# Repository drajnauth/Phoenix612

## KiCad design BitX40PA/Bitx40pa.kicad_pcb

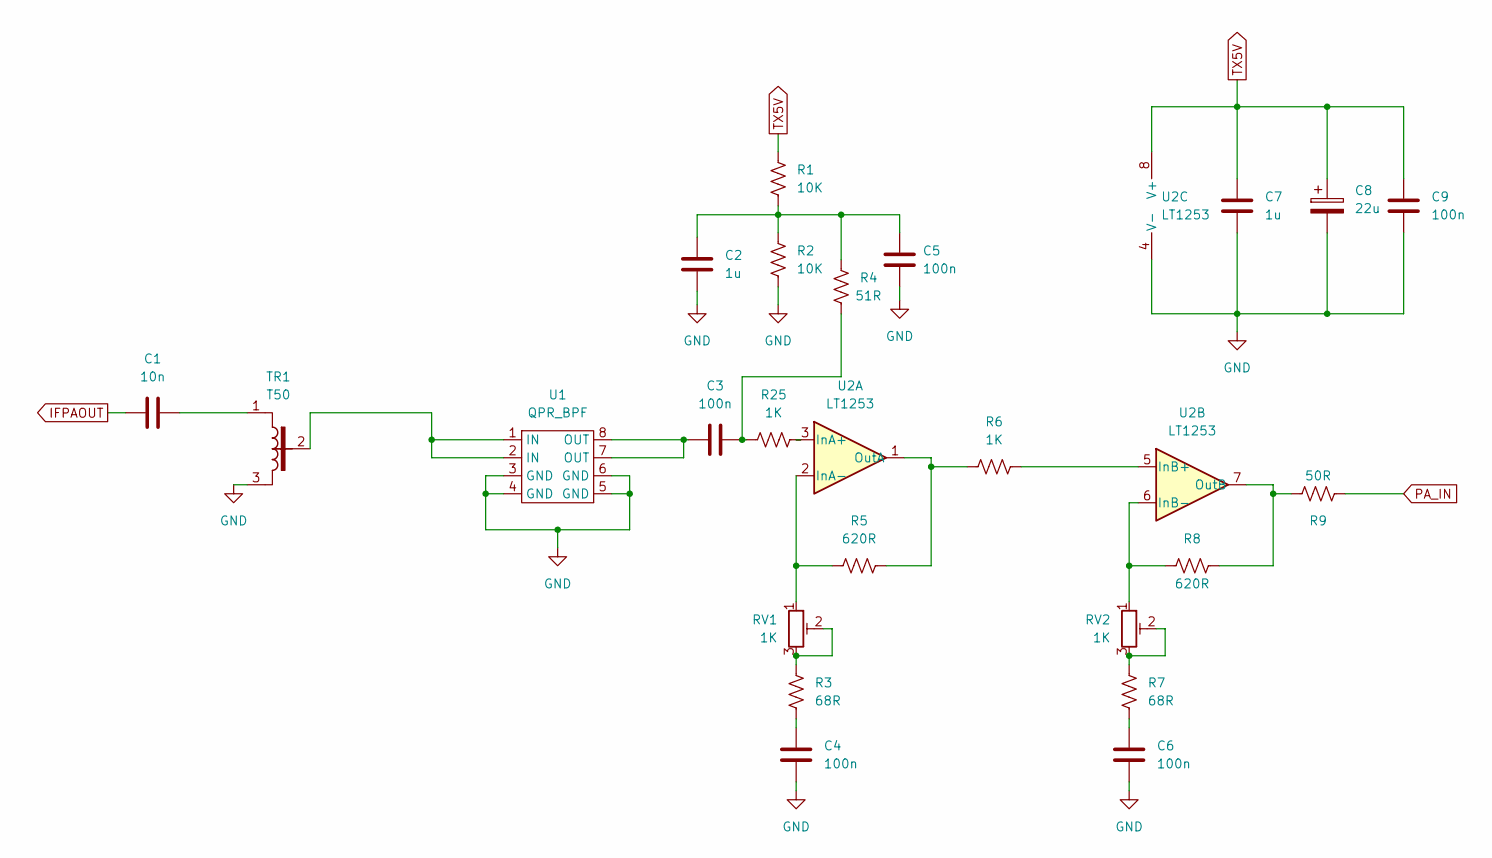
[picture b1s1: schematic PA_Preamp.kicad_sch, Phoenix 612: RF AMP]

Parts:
C1: 10n; C_1206_3216Metric
C2, C7: 1u; C_1206_3216Metric
C3, C4, C5, C6, C9: 100n; C_1206_3216Metric
C8: 22u; CP_Radial_D8.0mm_P2.50mm
R1, R2: 10K; R_1206_3216Metric
R3, R7: 68R; R_1206_3216Metric
R4: 51R; R_1206_3216Metric
R5, R8: 620R; R_1206_3216Metric
R6, R25: 1K; R_1206_3216Metric
R9: 50R; R_1206_3216Metric
RV1, RV2: 1K; Potentiometer_Bourns_3296W_Vertical
TR1: T50; T50-1Tap-Close
U1: QPR_BPF; QRPLabs_Filter_TH
U2: LT1253; DIP-8_W7.62mm

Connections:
GND: C2.2, C4.2, C5.2, C6.2, C7.2, C8.2, C9.2, R2.2, TR1.3, U1.3 (GND), U1.4 (GND), U1.5 (GND), U1.6 (GND), U2.4 (V-); also elsewhere on the board
IFPAOUT: C1.1; also elsewhere on the board
unnamed: C1.2, TR1.1
unnamed: C2.1, C5.1, R1.2, R2.1, R4.2
unnamed: C3.1, U1.7 (OUT), U1.8 (OUT)
unnamed: C3.2, R4.1, R25.1
unnamed: C4.1, R3.2
unnamed: C6.1, R7.2
unnamed: R3.1, RV1.2, RV1.3
unnamed: R5.1, RV1.1, U2.2 (InA-)
unnamed: R5.2, R6.1, U2.1 (OutA)
unnamed: R6.2, U2.5 (InB+)
unnamed: R7.1, RV2.2, RV2.3
unnamed: R8.1, R9.1, U2.7 (OutB)
unnamed: R8.2, RV2.1, U2.6 (InB-)
unnamed: R25.2, U2.3 (InA+)
unnamed: TR1.2, U1.1 (IN), U1.2 (IN)
PA_IN: R9.2; also elsewhere on the board
TX5V: C7.1, C8.1, C9.1, R1.1, U2.8 (V+); also elsewhere on the board

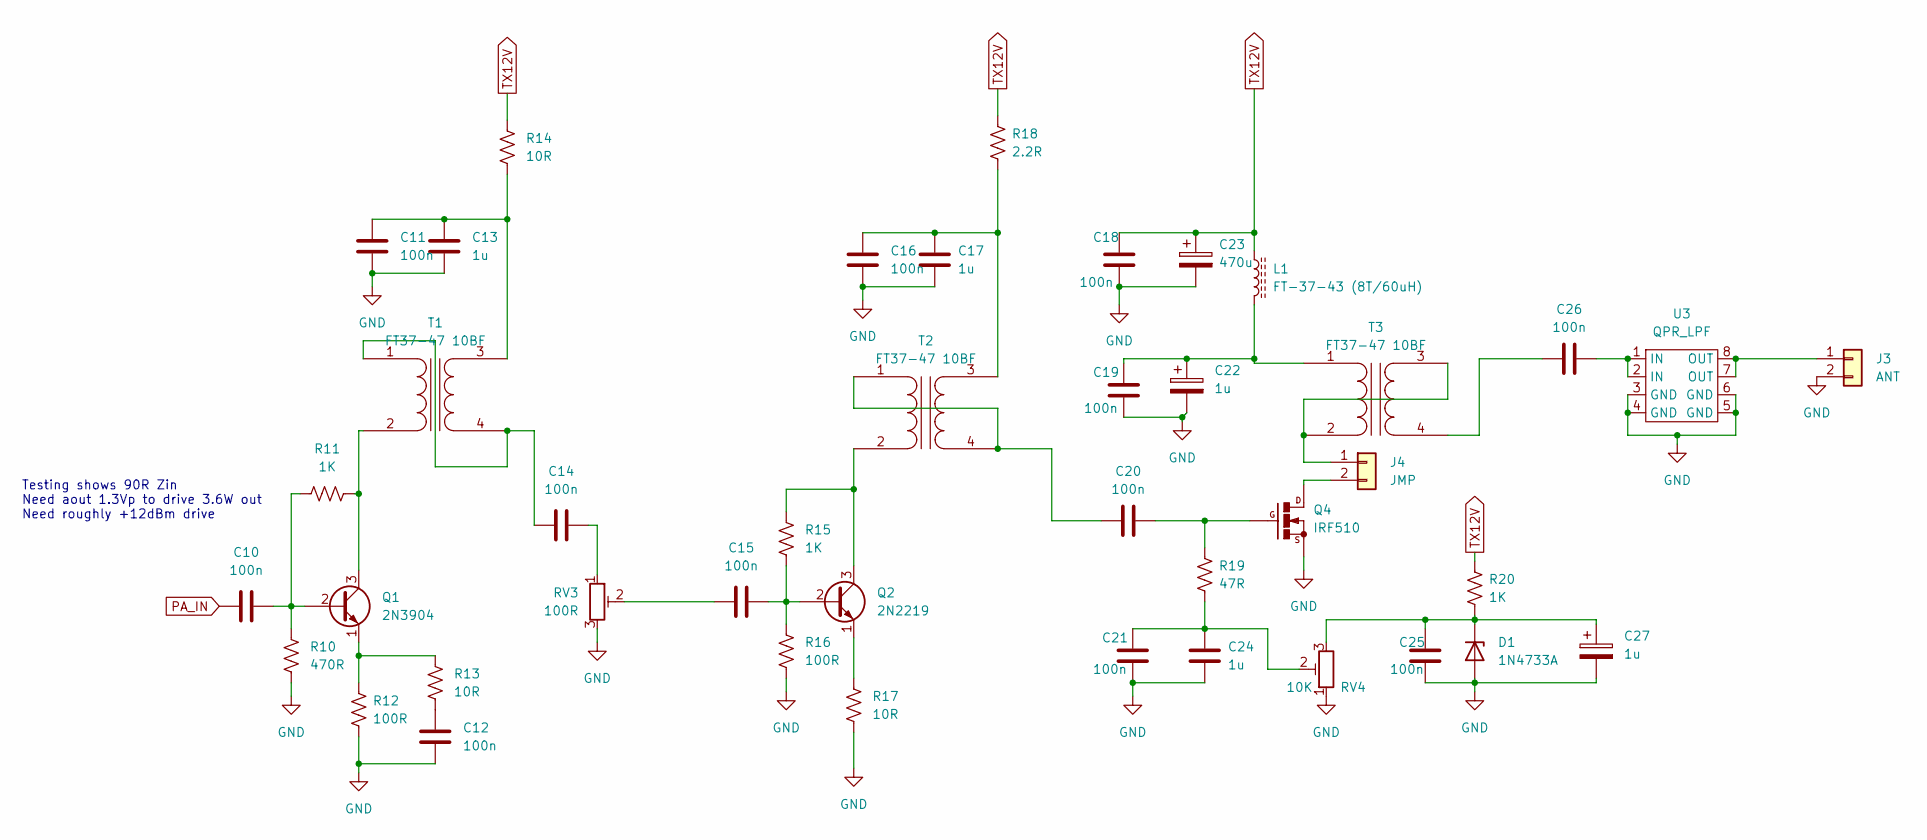
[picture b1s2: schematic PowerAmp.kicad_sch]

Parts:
C10, C11, C12, C14, C15, C16, C18, C19, C20, C21, C25, C26: 100n; C_1206_3216Metric
C13, C17, C24: 1u; C_1206_3216Metric
C22, C27: 1u; CP_Radial_D8.0mm_P2.50mm
C23: 470u; CP_Radial_D8.0mm_P2.50mm
D1: 1N4733A; D_DO-41_SOD81_P10.16mm_Horizontal
J3: ANT; PinHeader_1x02_P2.54mm_Vertical
J4: JMP; PinHeader_1x02_P2.54mm_Vertical
L1: FT-37-43 (8T/60uH); L_Toroid_Horizontal_D9.5mm_P15.00mm_Diameter10-5mm_Amidon-T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
Q1: 2N3904; TO-92_Inline
Q2: 2N2219; TO-39-3
Q4: IRF510; TO-220-3_Vertical
R10: 470R; R_1206_3216Metric
R11, R15, R20: 1K; R_1206_3216Metric
R12, R16: 100R; R_1206_3216Metric
R13, R14, R17: 10R; R_1206_3216Metric
R18: 2.2R; R_1206_3216Metric
R19: 47R; R_1206_3216Metric
RV3: 100R; Potentiometer_Bourns_3296W_Vertical
RV4: 10K; Potentiometer_Bourns_3296W_Vertical
T1, T2, T3: FT37-47 10BF; Transformer_Toroid_Horizontal_D10.5mm_Amidon-T37
U3: QPR_LPF; QRPLabs_Filter_TH

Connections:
GND: C11.2, C12.2, C13.2, C16.2, C17.2, C18.2, C19.2, C21.2, C22.2, C23.2, C24.2, C25.2, C27.2, D1.2 (A), J3.2, Q4.1, R10.1, R12.1, R16.1, R17.1, RV3.3, RV4.1, U3.3 (GND), U3.4 (GND), U3.5 (GND), U3.6 (GND); also elsewhere on the board
unnamed: C10.2, Q1.2 (B), R10.2, R11.1
unnamed: C11.1, C13.1, R14.1, T1.3 (SB)
unnamed: C12.1, R13.1
unnamed: C14.1, T1.1 (AA), T1.4 (SA)
unnamed: C14.2, RV3.1
unnamed: C15.1, RV3.2
unnamed: C15.2, Q2.2 (B), R15.1, R16.2
unnamed: C16.1, C17.1, R18.1, T2.3 (SB)
unnamed: C19.1, C22.1, L1.2, T3.1 (AA)
unnamed: C20.1, T2.1 (AA), T2.4 (SA)
unnamed: C20.2, Q4.3, R19.2
unnamed: C21.1, C24.1, R19.1, RV4.2
unnamed: C25.1, C27.1, D1.1 (K), R20.2, RV4.3
unnamed: C26.1, T3.4 (SA)
unnamed: C26.2, U3.1 (IN), U3.2 (IN)
unnamed: J3.1, U3.7 (OUT), U3.8 (OUT)
unnamed: Q1.1 (E), R12.2, R13.2
unnamed: Q1.3 (C), R11.2, T1.2 (AB)
unnamed: Q2.1 (E), R17.2
unnamed: Q2.3 (C), R15.2, T2.2 (AB)
unnamed: J4.2, Q4.2
unnamed: J4.1, T3.2 (AB), T3.3 (SB)
PA_IN: C10.1; also elsewhere on the board
TX12V: C18.1, C23.1, L1.1, R14.2, R18.2, R20.1; also elsewhere on the board

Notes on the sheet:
Testing shows 90R Zin Need aout 1.3Vp to drive 3.6W out Need roughly +12dBm drive

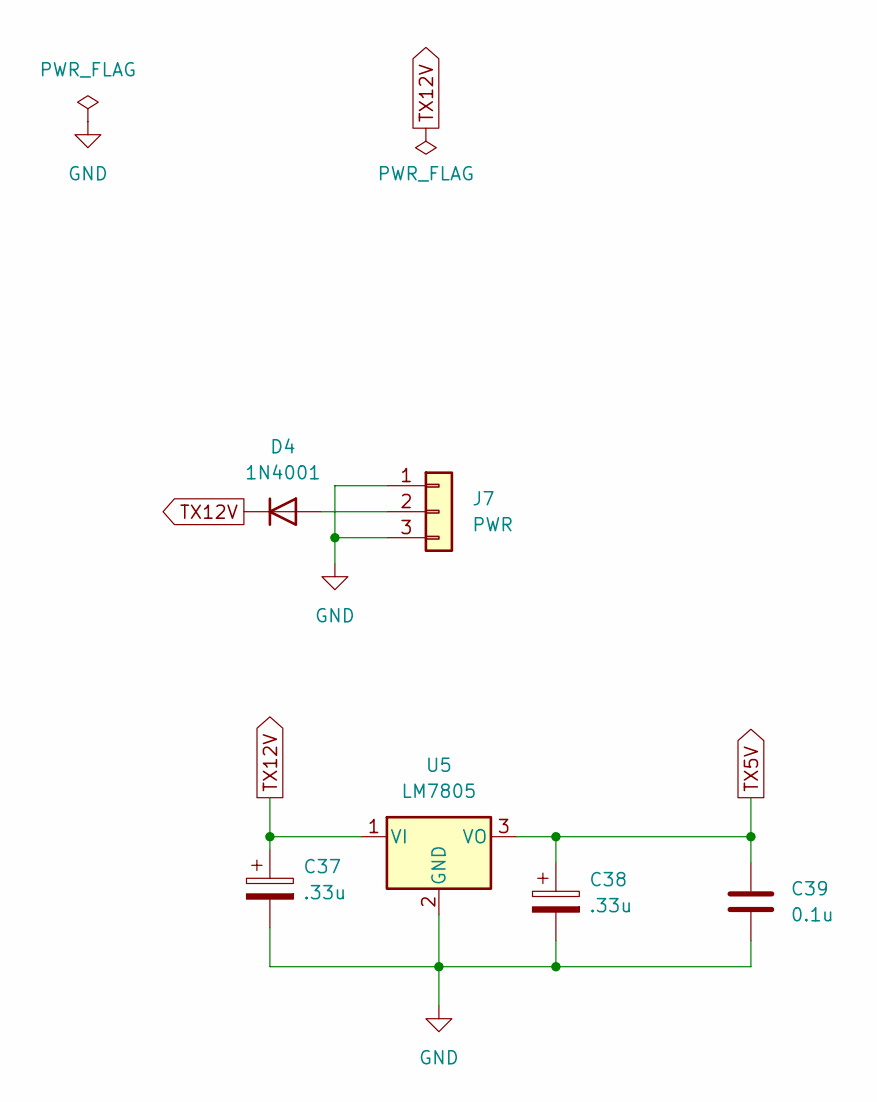
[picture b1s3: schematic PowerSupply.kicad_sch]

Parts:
C37, C38: .33u; CP_Radial_D8.0mm_P2.50mm
C39: 0.1u; C_1206_3216Metric
D4: 1N4001; D_DO-41_SOD81_P10.16mm_Horizontal
J7: PWR; PinHeader_1x03_P2.54mm_Vertical
U5: LM7805; TO-220-3_Vertical

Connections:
GND: C37.2, C38.2, C39.2, J7.1, J7.3, U5.2 (GND); also elsewhere on the board
unnamed: D4.2 (A), J7.2
TX5V: C38.1, C39.1, U5.3 (VO); also elsewhere on the board
TX12V: C37.1, D4.1 (K), U5.1 (VI); also elsewhere on the board

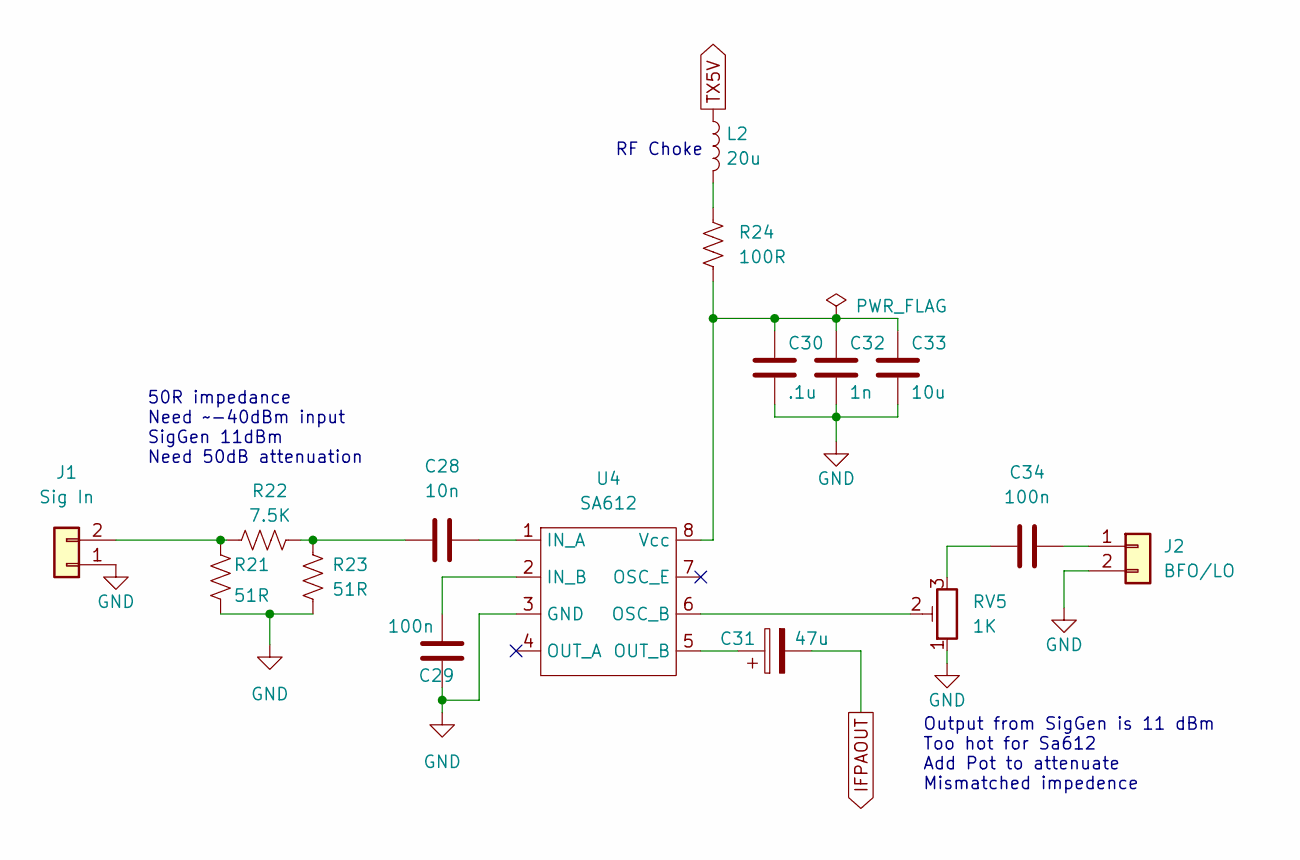
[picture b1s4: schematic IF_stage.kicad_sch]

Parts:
C28: 10n; C_1206_3216Metric
C29, C34: 100n; C_1206_3216Metric
C30: .1u; C_1206_3216Metric
C31: 47u; CP_Radial_D8.0mm_P2.50mm
C32: 1n; C_1206_3216Metric
C33: 10u; C_1206_3216Metric
J1: Sig In; PinHeader_1x02_P2.54mm_Vertical
J2: BFO/LO; PinHeader_1x02_P2.54mm_Vertical
L2: 20u; L_1206_3216Metric
R21, R23: 51R; R_1206_3216Metric
R22: 7.5K; R_1206_3216Metric
R24: 100R; R_1206_3216Metric
RV5: 1K; Potentiometer_Bourns_3296W_Vertical
U4: SA612; DIP-8_W7.62mm_Socket

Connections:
GND: C29.2, C30.2, C32.2, C33.2, J1.1, J2.2, R21.2, R23.2, RV5.1, U4.3 (GND); also elsewhere on the board
IFPAOUT: C31.2; also elsewhere on the board
unnamed: C28.1, R22.2, R23.1
unnamed: C28.2, U4.1 (IN_A)
unnamed: C29.1, U4.2 (IN_B)
unnamed: C30.1, C32.1, C33.1, R24.2, U4.8 (Vcc)
unnamed: C31.1, U4.5 (OUT_B)
unnamed: C34.1, J2.1
unnamed: C34.2, RV5.3
unnamed: J1.2, R21.1, R22.1
unnamed: L2.2, R24.1
unnamed: RV5.2, U4.6 (OSC_B)
TX5V: L2.1; also elsewhere on the board

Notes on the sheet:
Output from SigGen is 11 dBm Too hot for Sa612 Add Pot to attenuate Mismatched impedence
RF Choke
50R impedance Need ~-40dBm input SigGen 11dBm Need 50dB attenuation

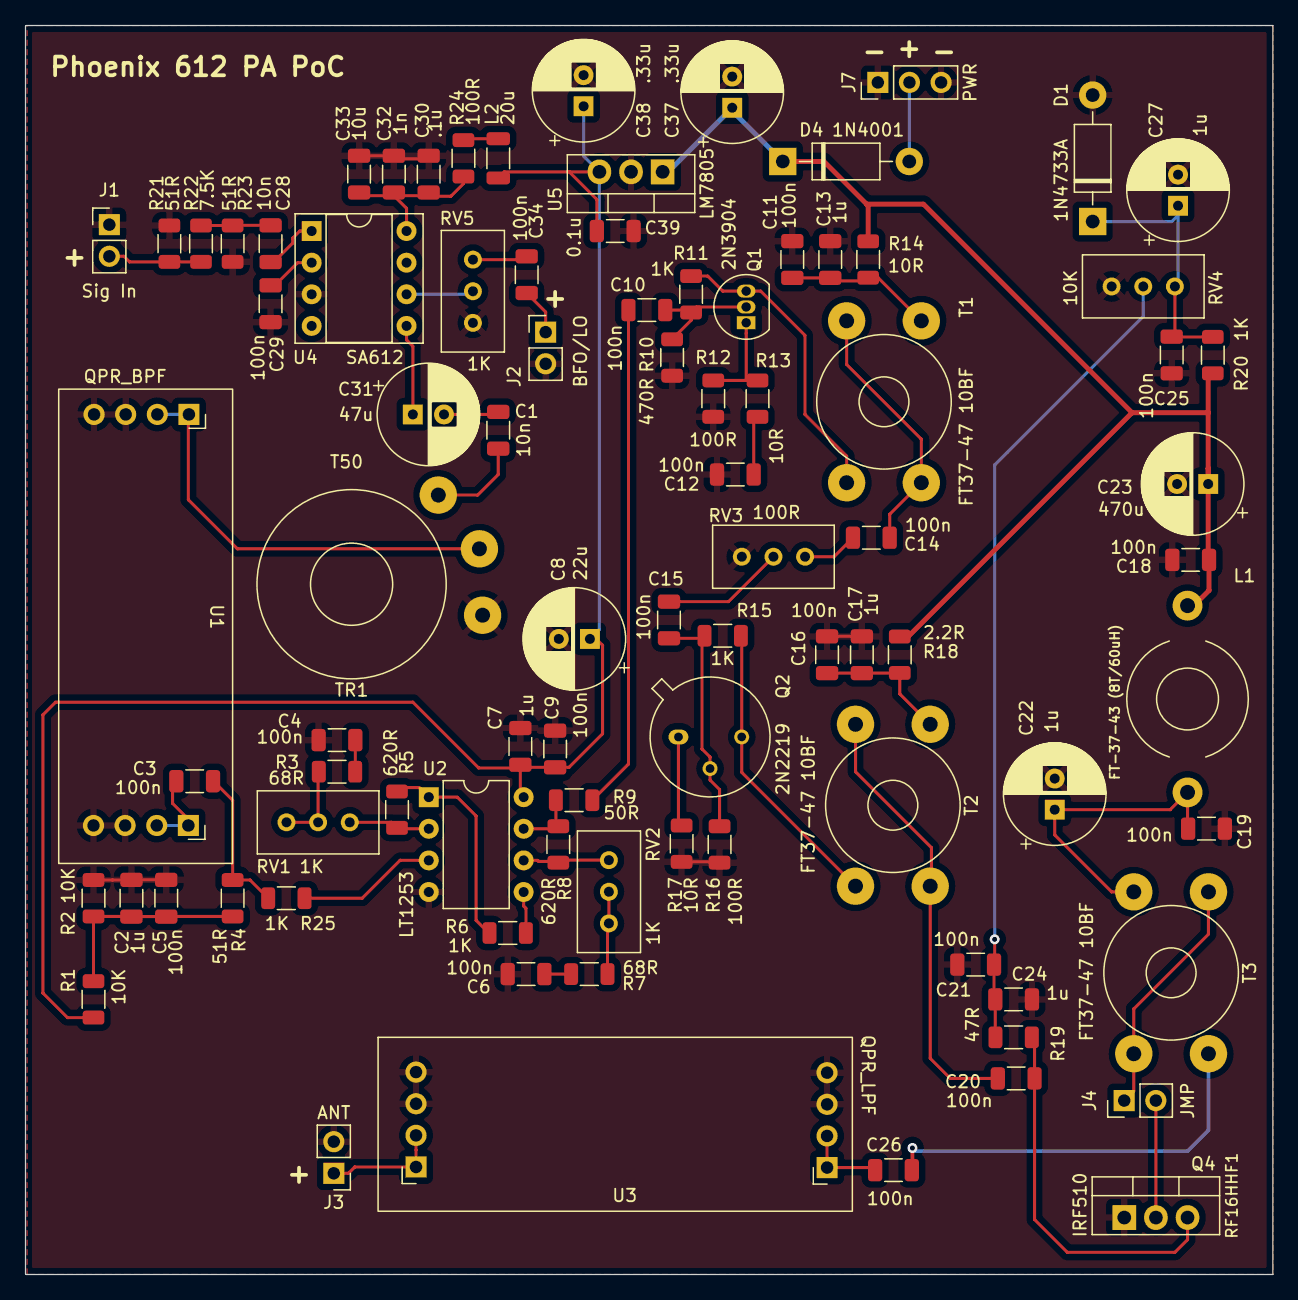
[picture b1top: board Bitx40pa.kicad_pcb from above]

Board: 2 copper layers, 100.2 x 100.3 mm, 88 parts (0 on the bottom side), 53 nets.

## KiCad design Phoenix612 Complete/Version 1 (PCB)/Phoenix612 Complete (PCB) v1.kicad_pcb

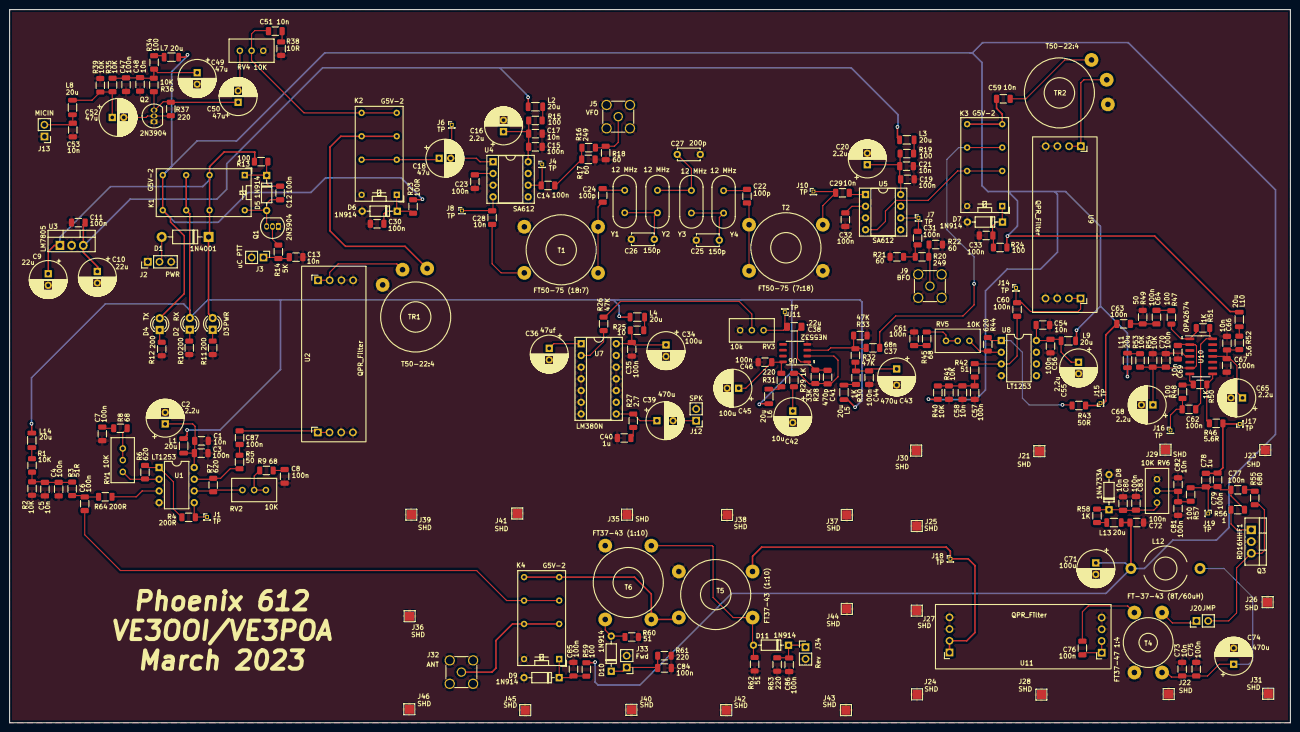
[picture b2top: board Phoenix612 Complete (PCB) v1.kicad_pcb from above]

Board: 2 copper layers, 277.9 x 154.7 mm, 257 parts (0 on the bottom side), 130 nets.

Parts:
C1, C5, C13, C17, C21, C28, C29, C48, C51, C53, C54, C58, C59, C66, C69, C73, C80, C82: 10n; C_1206_3216Metric
C2, C16, C20, C55, C65, C68: 2.2u; CP_Radial_D8.0mm_P2.50mm
C3, C4, C6, C7, C8, C11, C12, C14, C15, C19, C23, C30, C31, C32, C33, C35, C44, C46, C47, C56, C57, C60, C61, C62, C63, C64, C67, C70, C72, C75, C76, C77, C79, C81, C83, C84, C85, C86, C87: 100n; C_1206_3216Metric
C9, C10: 22u; CP_Radial_D8.0mm_P2.50mm
C18, C49, C50, C52: 47u; CP_Radial_D8.0mm_P2.50mm
C22, C24: 100p; C_1206_3216Metric
C25, C26: 150p; C_Disc_D4.7mm_W2.5mm_P5.00mm
C27: 200p; C_Disc_D4.7mm_W2.5mm_P5.00mm
C34, C45, C71: 100u; CP_Radial_D8.0mm_P2.50mm
C36: 47uf; CP_Radial_D8.0mm_P2.50mm
C37: 68n; C_1206_3216Metric
C38: .22u; C_1206_3216Metric_Pad1.33x1.80mm_HandSolder
C39, C43, C74: 470u; CP_Radial_D8.0mm_P3.50mm
C40, C78: 1u; C_1206_3216Metric
C41: 470p; C_1206_3216Metric
C42: 10u; CP_Radial_D8.0mm_P2.50mm
D1: 1N4001; D_DO-41_SOD81_P10.16mm_Horizontal
D2: RX; LED_D3.0mm
D3: PWR; LED_D3.0mm
D4: TX; LED_D3.0mm
D5, D6, D7, D9, D10, D11: 1N914; D_DO-35_SOD27_P7.62mm_Horizontal
D8: 1N4733A; D_DO-35_SOD27_P7.62mm_Horizontal
J1, J4, J6, J7, J8, J10, J11, J14, J15, J16, J17, J18, J19: TP; PinHeader_1x01_P1.00mm_Vertical
J2: PWR; PinHeader_1x03_P2.54mm_Vertical
J3: uC PTT; PinHeader_1x02_P2.54mm_Vertical
J5: VFO; SMA_Amphenol_901-144_Vertical
J9: BFO; SMA_Amphenol_901-144_Vertical
J12: SPK; PinHeader_1x02_P2.54mm_Vertical
J13: MICIN; PinHeader_1x02_P2.54mm_Vertical
J20: JMP; PinHeader_1x02_P2.54mm_Vertical
J21, J22, J23, J24, J25, J26, J27, J28, J29, J30, J31, J35, J36, J37, J38, J39, J40, J41, J42, J43, J44, J45, J46: SHD; TestPoint_Pad_2.0x2.0mm
J32: ANT; SMA_Amphenol_901-144_Vertical
J33: Fwd; PinHeader_1x02_P2.54mm_Vertical
J34: Rev; PinHeader_1x02_P2.54mm_Vertical
K1, K2, K3, K4: G5V-2; Relay_DPDT_Omron_G5V-2
L1, L2, L3, L4, L5, L6, L7, L8, L9, L10, L11, L13, L14: 20u; L_1206_3216Metric
L12: FT-37-43 (8T/60uH); L_Toroid_Horizontal_D9.5mm_P15.00mm_Diameter10-5mm_Amidon-T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
Q1, Q2: 2N3904; TO-92_Inline
Q3: RD16HHF1; TO-220-3
R1, R2, R35, R36, R39, R40, R41, R53, R54: 10K; R_1206_3216Metric
R3: 51R; R_1206_3216Metric
R4, R64: 200R; R_1206_3216Metric
R5, R49: 50; R_1206_3216Metric
R6, R7, R44: 620; R_1206_3216Metric
R8, R9, R45: 68; R_1206_3216Metric
R10, R11, R12: 200; R_1206_3216Metric
R13, R15, R19, R24, R34, R47, R48, R57, R59: 100; R_1206_3216Metric
R14: 5K; R_1206_3216Metric
R16, R20: 249; R_1206_3216Metric
R17, R18, R21, R22: 60; R_1206_3216Metric
R23: 100R; R_1206_3216Metric
R25: 10; R_1206_3216Metric
R26, R32, R33: 47K; R_1206_3216Metric
R27: 2.7; R_1206_3216Metric
R28: 33K; R_1206_3216Metric
R29, R30, R50, R51, R58: 1K; R_1206_3216Metric
R31, R37, R61, R63: 220; R_1206_3216Metric
R38: 10R; R_1206_3216Metric
R42, R60, R62: 51; R_1206_3216Metric
R43: 50R; R_1206_3216Metric
R46: 5.6R; R_1206_3216Metric
R52: 5.6; R_1206_3216Metric
R55: 680; R_1206_3216Metric
R56: 1; R_1206_3216Metric
RV1, RV2, RV4, RV5, RV6: 10K; Potentiometer_Bourns_3296W_Vertical
RV3: 10k; Potentiometer_Bourns_3296W_Vertical
T1: FT50-75 (18:7); Transformer_Toroid_Horizontal_D14.0mm_Amidon-T50
T2: FT50-75 (7:18); Transformer_Toroid_Horizontal_D14.0mm_Amidon-T50
T4: FT37-47 1:4; Transformer_Toroid_Horizontal_D10.5mm_Amidon-T37
T5, T6: FT37-43 (1:10); Transformer_Toroid_Horizontal_D14.0mm_Amidon-T50
TR1, TR2: T50-22:4; T50-1Tap-Close
U1, U8: LT1253; DIP-8_W7.62mm
U2, U9, U11: QPR_Filter; QRPLabs_Filter_TH
U3: LM7805; TO-220-3_Vertical
U4, U5: SA612; DIP-8_W7.62mm_Socket
U6: NE5532; SOP-8_3.9x4.9mm_P1.27mm
U7: LM380N; DIP-14_W7.62mm_Socket
U10: OPA2674; SOIC-14_3.9x8.7mm_P1.27mm
Y1, Y2, Y3, Y4: 12 MHz; Crystal_HC49-4H_Vertical

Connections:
5V: C10.1, C11.1, L2.1, L3.1, U3.3 (VO)
12V: C9.1, D1.1 (K), D3.2 (A), K1.4, K1.13, R13.2, U3.1 (VI)
AF_12V: C45.1, C46.1, R31.2, U6.8 (V+)
AF_BIAS: C37.2, R32.1, R33.1, U6.3 (+)
ANT: J32.1 (In), K4.4, K4.13
ANT_IN: C6.1, K4.6, K4.11
ANT_OUT: K4.8, K4.9, T5.4 (SB), T6.1 (AA)
GND: C1.2, C2.2, C3.2, C4.2, C5.2, C7.2, C8.2, C9.2, C10.2, C11.2, C13.1, C15.2, C16.2, C17.2, C19.2, C20.2, C21.2, C23.2, C25.2, C26.2, C27.2, C30.2, C32.2, C33.2, C34.2, C35.2, C36.2, C40.2, C42.2, C43.2, C44.2, C45.2, C46.2, C47.2, C48.2, C49.2, C53.2, C54.2, C55.2, C56.2, C57.2, C58.2, C61.2, C65.2, C66.2, C67.2, C68.2, C69.2, C70.2, C71.2, C72.2, C73.2, C74.2, C75.2, C80.2, C81.2, C82.2, C83.2, C84.2, C85.2, C86.2, D6.2 (A), D7.2 (A), D8.2 (A), D9.2 (A), J2.1, J2.3, J3.2, J5.2 (Ext), J9.2 (Ext), J12.2, J13.1, J21.1, J22.1, J23.1, J24.1, J25.1, J26.1, J27.1, J28.1, J29.1, J30.1, J31.1, J32.2 (Ext), J33.2, J34.2, J35.1, J36.1, J37.1, J38.1, J39.1, J40.1, J41.1, J42.1, J43.1, J44.1, J45.1, J46.1, K2.16, K3.16, K4.16, Q1.1 (E), Q2.1 (E), Q3.2, R2.2, R10.2, R11.2, R12.2, R17.2, R18.2, R21.2, R22.2, R33.2, R38.1, R39.2, R41.2, R49.1, R54.2, R60.1, R61.1, R62.1, R63.1, RV3.3, RV4.3, RV6.1, T1.3 (SA), T2.2 (AB), T4.3 (SB), T5.2 (AB), T6.4 (SB), TR1.1, TR2.3, U1.4 (V-), U2.3 (GND), U2.4 (GND), U2.5 (GND), U2.6 (GND), U3.2 (GND), U4.3 (GND), U5.3 (GND), U6.4 (V-), U7.3 (GND), U7.4 (GND), U7.5 (GND), U7.6 (-), U7.7 (GND), U7.10 (GND), U7.11 (GND), U7.12 (GND), U8.4 (V-), U9.3 (GND), U9.4 (GND), U9.5 (GND), U9.6 (GND), U10.4 (V-), U11.3 (GND), U11.4 (GND), U11.5 (GND), U11.6 (GND)
IFAFOUT: C37.1, K3.6, K3.11
IFMICIN: C51.1, K2.8, K2.9, RV4.2
IFPAOUT: C59.1, K3.8, K3.9
IFRFIN: K2.6, K2.11, TR1.3
M2_12V: C73.1, C74.1, C75.1, L12.2, T4.1 (AA)
unnamed: C1.1, C2.1, C3.1, L1.2, U1.8 (V+)
unnamed: C4.1, C5.1, R1.2, R2.1, R3.2
unnamed: C6.2, R3.1, R64.1
unnamed: C7.1, R8.2
unnamed: C8.1, R9.2
unnamed: C12.1, D5.1 (K), K1.1, R13.1
unnamed: C12.2, D5.2 (A), K1.16, Q1.3 (C)
unnamed: C13.2, J3.1, R14.2
unnamed: C14.1, R16.1, R17.1
unnamed: C14.2, J4.1, U4.6 (OSC_B)
unnamed: C15.1, C16.1, C17.1, R15.2, U4.8 (Vcc)
unnamed: C18.1, K2.4, K2.13
unnamed: C18.2, J6.1, U4.1 (IN_A)
unnamed: C19.1, C20.1, C21.1, R19.2, U5.8 (Vcc)
unnamed: C22.1, Y4.2
unnamed: C22.2, T2.1 (AA), T2.3 (SA)
unnamed: C23.1, U4.2 (IN_B)
unnamed: C24.1, T1.2 (AB), T1.4 (SB)
unnamed: C24.2, Y1.1
unnamed: C25.1, Y3.2, Y4.1
unnamed: C26.1, Y1.2, Y2.1
unnamed: C27.1, Y2.2, Y3.1
unnamed: C28.1, J8.1, U4.4 (OUT_A)
unnamed: C28.2, T1.1 (AA)
unnamed: C29.1, J10.1, T2.4 (SB)
unnamed: C29.2, U5.1 (IN_A)
unnamed: C30.1, D6.1 (K), K2.1, R23.1
unnamed: C31.1, R20.1, R21.1
unnamed: C31.2, J7.1, U5.6 (OSC_B)
unnamed: C32.1, U5.2 (IN_B)
unnamed: C33.1, D7.1 (K), K3.1, R24.1
unnamed: C34.1, C35.1, R25.2, U7.14 (VS)
unnamed: C36.1, U7.1 (BYPASS)
unnamed: C38.1, C41.2, R28.2, U6.1
unnamed: C38.2, J11.1, RV3.1
unnamed: C39.1, R27.1, U7.8
unnamed: C39.2, J12.1
unnamed: C40.1, R27.2
unnamed: C41.1, R28.1, R29.1, U6.2 (-)
unnamed: C42.1, R29.2
unnamed: C43.1, C44.1, R30.2, R32.2
unnamed: C47.1, C48.1, C49.1, R34.2, R35.1, R36.1
unnamed: C50.1, Q2.3 (C), R36.2, R37.2
unnamed: C50.2, RV4.1
unnamed: C51.2, R38.2
unnamed: C52.1, L8.2, R35.2, R39.1
unnamed: C52.2, Q2.2 (B), R37.1
unnamed: C53.1, J13.2, L8.1
unnamed: C54.1, C55.1, C56.1, L9.2, U8.8 (V+)
unnamed: C57.1, C58.1, R40.2, R41.1, R42.2
unnamed: C59.2, TR2.1
unnamed: C60.1, J14.1, U9.7 (OUT), U9.8 (OUT)
unnamed: C60.2, R42.1, U8.3 (InA+)
unnamed: C61.1, R45.2
unnamed: C62.1, R51.2, U10.14
unnamed: C62.2, J16.1, R48.1
unnamed: C63.2, C64.1, R49.2
unnamed: C64.2, R47.1
unnamed: C76.1, T4.4 (SA)
unnamed: C76.2, U11.1 (IN), U11.2 (IN)
unnamed: C77.1, R55.2
unnamed: C77.2, C78.1, C79.1, J19.1, R56.2, R57.2
unnamed: C80.1, C83.1, D8.1 (K), R58.2, RV6.3
unnamed: C81.1, C82.1, R57.1, RV6.2
unnamed: C84.1, D10.1 (K), J33.1, R61.2
unnamed: C85.1, D9.1 (K), K4.1, R59.1
unnamed: C86.1, D11.1 (K), J34.1, R63.2
unnamed: D1.2 (A), J2.2
unnamed: D2.1 (K), R10.1
unnamed: D3.1 (K), R11.1
unnamed: D4.1 (K), R12.1
unnamed: D10.2 (A), R60.2, T6.3 (SA)
unnamed: D11.2 (A), R62.2, T5.3 (SA), T6.2 (AB)
unnamed: J1.1, R4.2, U1.5 (InB+)
unnamed: J5.1 (In), R16.2, R18.1
unnamed: J9.1 (In), R20.2, R22.1
unnamed: J20.1, T4.2 (AB)
unnamed: J20.2, Q3.3, R55.1
unnamed: K3.4, K3.13, U5.4 (OUT_A)
unnamed: L2.2, R15.1
unnamed: L3.2, R19.1
unnamed: L4.2, R25.1
unnamed: L5.2, R30.1
unnamed: L6.2, R31.1
unnamed: L7.2, R34.1
unnamed: L10.1, R52.1
unnamed: L11.1, R53.1
unnamed: L13.1, R58.1
unnamed: Q1.2 (B), R14.1
unnamed: Q3.1, R56.1
unnamed: L14.2, R1.1
unnamed: R4.1, R6.2, U1.1 (OutA)
unnamed: R5.1, R7.1, U1.7 (OutB)
unnamed: C87.1, R5.2
unnamed: R6.1, RV1.1, U1.2 (InA-)
unnamed: R7.2, RV2.1, U1.6 (InB-)
unnamed: R8.1, RV1.2, RV1.3
unnamed: R9.1, RV2.2, RV2.3
unnamed: R26.1, RV3.2
unnamed: R26.2, U7.2 (+)
unnamed: R43.1, R44.2, U8.1 (OutA)
unnamed: R44.1, RV5.1, U8.2 (InA-)
unnamed: R45.1, RV5.2, RV5.3
unnamed: R46.1, R50.2, U10.8
unnamed: R47.2, R51.1, U10.1 (-)
unnamed: R48.2, R50.1, U10.7 (-)
unnamed: R64.2, U1.3 (InA+)
unnamed: C87.2, U2.1 (IN), U2.2 (IN)
unnamed: TR1.2, U2.7 (OUT), U2.8 (OUT)
unnamed: TR2.2, U9.1 (IN), U9.2 (IN)
PA_DRIVER_IN: C63.1, J15.1, R43.2
PA_IN: C78.2, C79.2, J17.1, R46.2
PA_OUT: J18.1, T5.1 (AA), U11.7 (OUT), U11.8 (OUT)
RX12V: D2.2 (A), K1.6, K1.11, L1.1, L4.1, L5.1, L6.1, L14.1
TX12V: C71.1, C72.1, D4.2 (A), K1.8, K1.9, L7.1, L9.1, L10.2, L11.2, L12.1, L13.2, R23.2, R24.2, R40.1, R59.2
U1_6V: C68.1, C69.1, C70.1, R53.2, R54.1, U10.2 (+), U10.6 (+)
U1_12V: C65.1, C66.1, C67.1, R52.2, U10.11 (V+)

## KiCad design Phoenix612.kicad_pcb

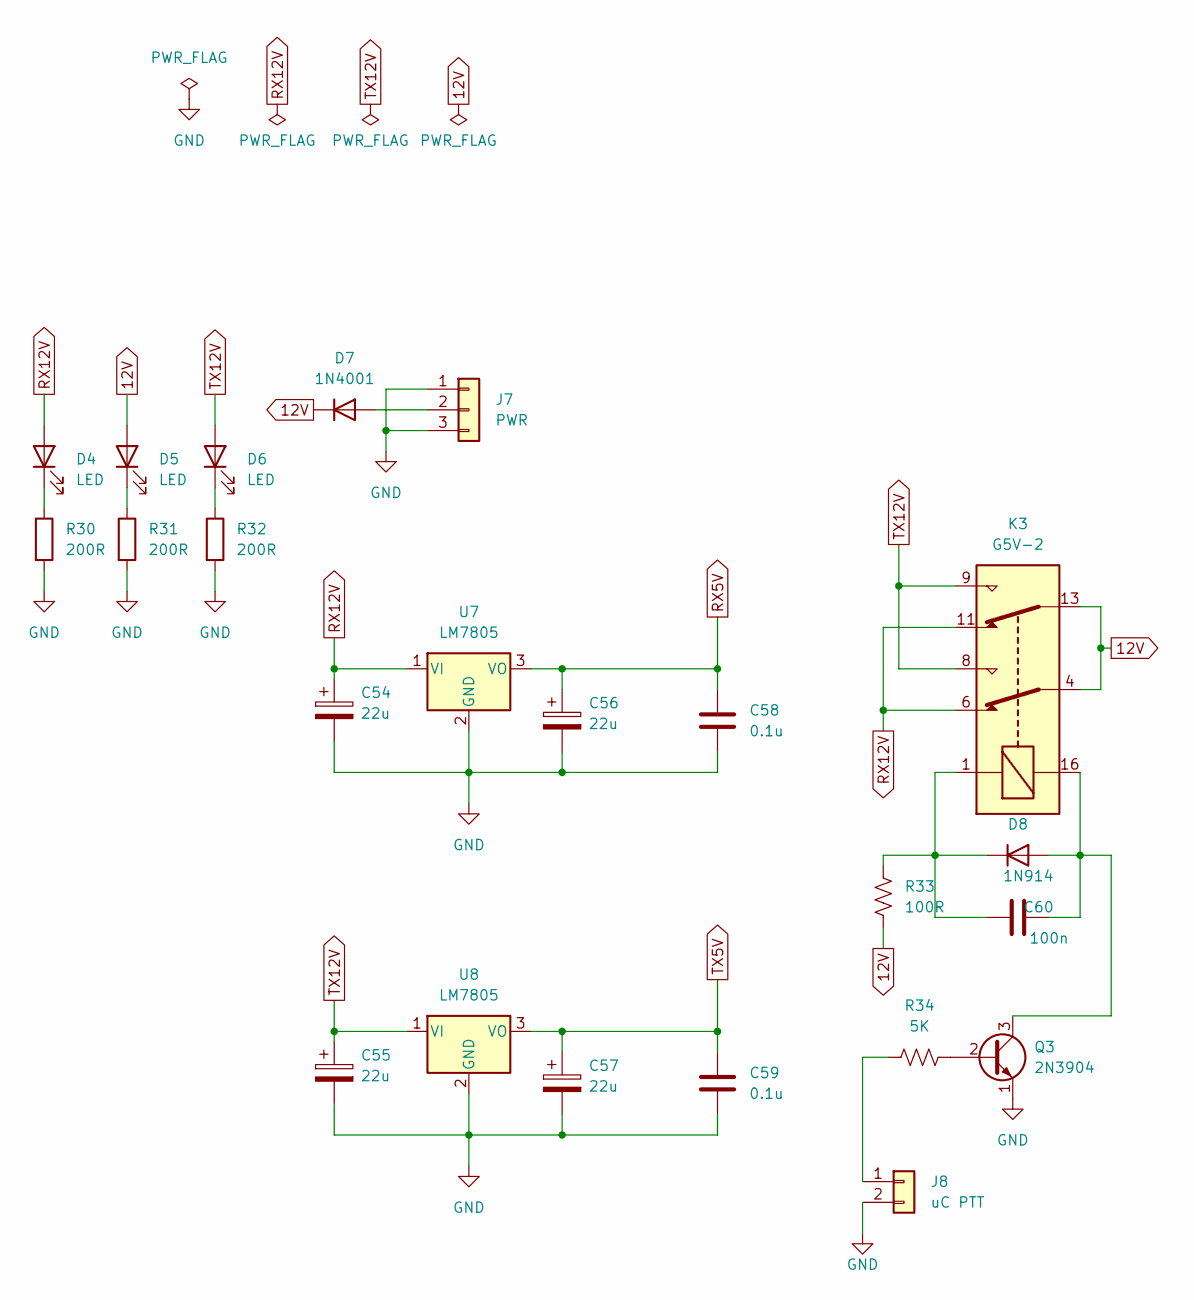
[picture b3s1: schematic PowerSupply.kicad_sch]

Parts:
C54, C55, C56, C57: 22u; CP_Radial_D8.0mm_P2.50mm
C58, C59: 0.1u; C_Disc_D3.0mm_W1.6mm_P2.50mm
C60: 100n; C_Disc_D3.4mm_W2.1mm_P2.50mm
D4, D5, D6: LED; LED_D3.0mm
D7: 1N4001; D_DO-41_SOD81_P10.16mm_Horizontal
D8: 1N914; D_DO-35_SOD27_P7.62mm_Horizontal
J7: PWR; PinHeader_1x03_P2.54mm_Vertical
J8: uC PTT; PinHeader_1x02_P2.54mm_Vertical
K3: G5V-2; Relay_DPDT_Omron_G5V-2
Q3: 2N3904; TO-92_Inline
R30, R31, R32: 200R; R_Axial_DIN0207_L6.3mm_D2.5mm_P10.16mm_Horizontal
R33: 100R; R_Axial_DIN0207_L6.3mm_D2.5mm_P10.16mm_Horizontal
R34: 5K; R_Axial_DIN0207_L6.3mm_D2.5mm_P10.16mm_Horizontal
U7, U8: LM7805; TO-220-3_Vertical

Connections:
12V: D5.2 (A), D7.1 (K), K3.4, K3.13, R33.2
GND: C54.2, C55.2, C56.2, C57.2, C58.2, C59.2, J7.1, J7.3, J8.2, Q3.1 (E), R30.2, R31.2, R32.2, U7.2 (GND), U8.2 (GND); also elsewhere on the board
unnamed: C60.1, D8.1 (K), K3.1, R33.1
unnamed: C60.2, D8.2 (A), K3.16, Q3.3 (C)
unnamed: D4.1 (K), R30.1
unnamed: D5.1 (K), R31.1
unnamed: D6.1 (K), R32.1
unnamed: D7.2 (A), J7.2
unnamed: J8.1, R34.2
unnamed: Q3.2 (B), R34.1
RX5V: C56.1, C58.1, U7.3 (VO); also elsewhere on the board
RX12V: C54.1, D4.2 (A), K3.6, K3.11, U7.1 (VI); also elsewhere on the board
TX5V: C57.1, C59.1, U8.3 (VO); also elsewhere on the board
TX12V: C55.1, D6.2 (A), K3.8, K3.9, U8.1 (VI); also elsewhere on the board

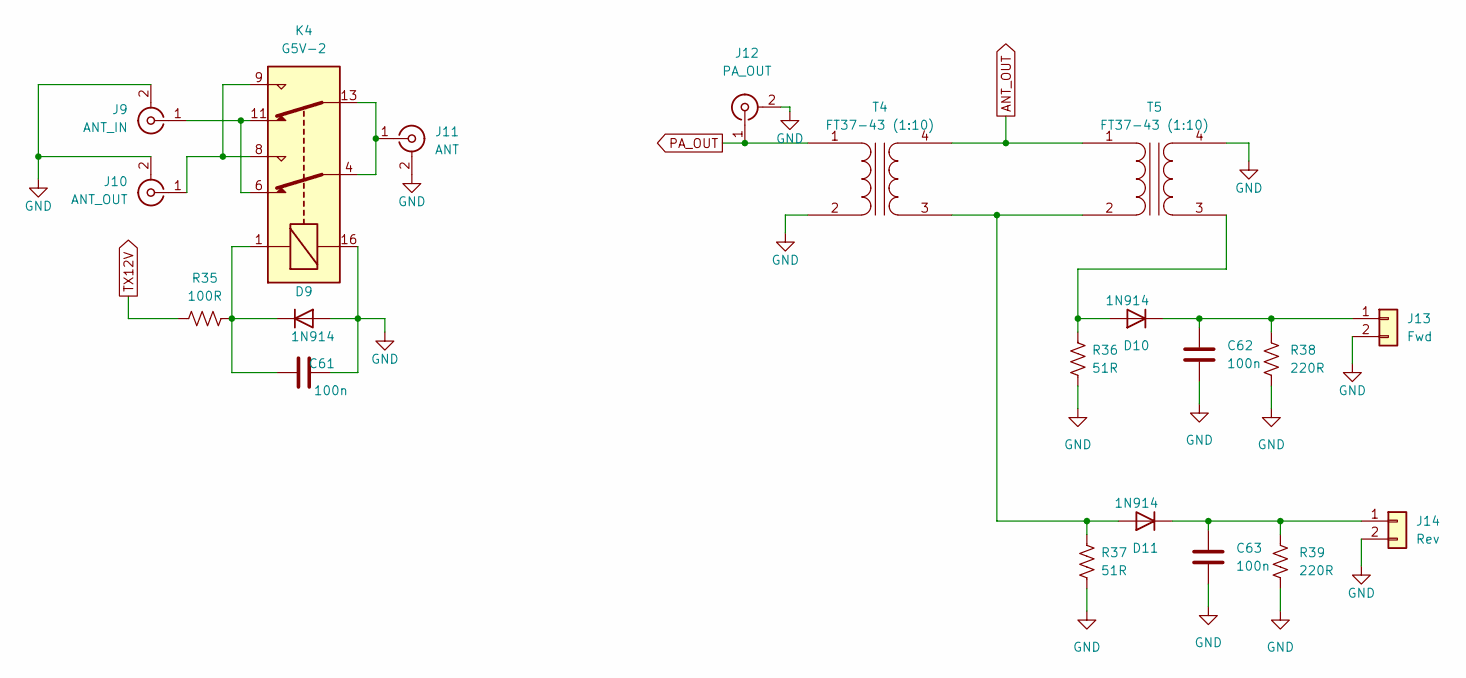
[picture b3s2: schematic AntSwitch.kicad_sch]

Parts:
C61, C62, C63: 100n; C_Disc_D3.4mm_W2.1mm_P2.50mm
D9, D10, D11: 1N914; D_DO-35_SOD27_P7.62mm_Horizontal
J9: ANT_IN; SMA_Amphenol_901-144_Vertical
J10: ANT_OUT; SMA_Amphenol_901-144_Vertical
J11: ANT; SMA_Amphenol_901-144_Vertical
J12: PA_OUT; SMA_Amphenol_901-144_Vertical
J13: Fwd; PinHeader_1x02_P2.54mm_Vertical
J14: Rev; PinHeader_1x02_P2.54mm_Vertical
K4: G5V-2; Relay_DPDT_Omron_G5V-2
R35: 100R; R_Axial_DIN0207_L6.3mm_D2.5mm_P10.16mm_Horizontal
R36, R37: 51R; R_Axial_DIN0207_L6.3mm_D2.5mm_P10.16mm_Horizontal
R38, R39: 220R; R_Axial_DIN0207_L6.3mm_D2.5mm_P10.16mm_Horizontal
T4, T5: FT37-43 (1:10); Transformer_Toroid_Horizontal_D14.0mm_Amidon-T50

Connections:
ANT_OUT: T4.4 (SB), T5.1 (AA)
GND: C61.2, C62.2, C63.2, D9.2 (A), J9.2 (Ext), J10.2 (Ext), J11.2 (Ext), J12.2 (Ext), J13.2, J14.2, K4.16, R36.1, R37.1, R38.1, R39.1, T4.2 (AB), T5.4 (SB); also elsewhere on the board
unnamed: C61.1, D9.1 (K), K4.1, R35.1
unnamed: C62.1, D10.1 (K), J13.1, R38.2
unnamed: C63.1, D11.1 (K), J14.1, R39.2
unnamed: D10.2 (A), R36.2, T5.3 (SA)
unnamed: D11.2 (A), R37.2, T4.3 (SA), T5.2 (AB)
unnamed: J9.1 (In), K4.6, K4.11
unnamed: J10.1 (In), K4.8, K4.9
unnamed: J11.1 (In), K4.4, K4.13
PA_OUT: J12.1 (In), T4.1 (AA)
TX12V: R35.2; also elsewhere on the board

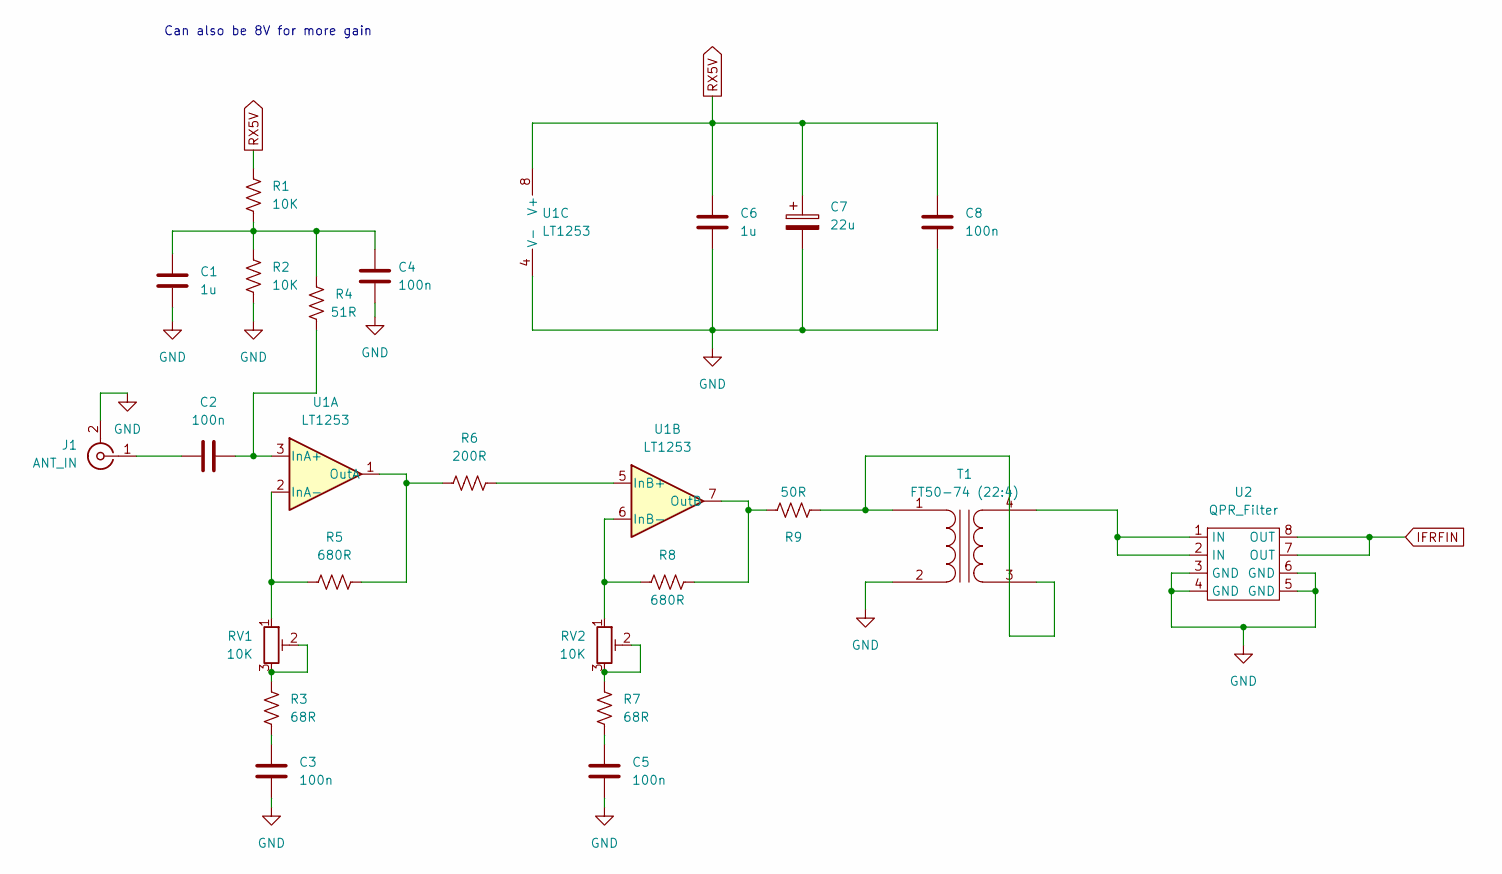
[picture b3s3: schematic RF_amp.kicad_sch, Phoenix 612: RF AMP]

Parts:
C1, C6: 1u; C_Disc_D3.4mm_W2.1mm_P2.50mm
C2, C3, C4, C5, C8: 100n; C_Disc_D3.4mm_W2.1mm_P2.50mm
C7: 22u; CP_Radial_D8.0mm_P2.50mm
J1: ANT_IN; SMA_Amphenol_901-144_Vertical
R1, R2: 10K; R_Axial_DIN0207_L6.3mm_D2.5mm_P10.16mm_Horizontal
R3, R7: 68R; R_Axial_DIN0207_L6.3mm_D2.5mm_P10.16mm_Horizontal
R4: 51R; R_Axial_DIN0207_L6.3mm_D2.5mm_P10.16mm_Horizontal
R5, R8: 680R; R_Axial_DIN0207_L6.3mm_D2.5mm_P10.16mm_Horizontal
R6: 200R; R_Axial_DIN0207_L6.3mm_D2.5mm_P10.16mm_Horizontal
R9: 50R; R_Axial_DIN0207_L6.3mm_D2.5mm_P10.16mm_Horizontal
RV1, RV2: 10K; Potentiometer_Bourns_3296W_Vertical
T1: FT50-74 (22:4); Transformer_Toroid_Horizontal_D14.0mm_Amidon-T50
U1: LT1253; DIP-8_W7.62mm
U2: QPR_Filter; QRPLabs_Filter_TH

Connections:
GND: C1.2, C3.2, C4.2, C5.2, C6.2, C7.2, C8.2, J1.2 (Ext), R2.2, T1.2 (AB), U1.4 (V-), U2.3 (GND), U2.4 (GND), U2.5 (GND), U2.6 (GND); also elsewhere on the board
IFRFIN: U2.7 (OUT), U2.8 (OUT); also elsewhere on the board
unnamed: C1.1, C4.1, R1.2, R2.1, R4.2
unnamed: C2.1, J1.1 (In)
unnamed: C2.2, R4.1, U1.3 (InA+)
unnamed: C3.1, R3.2
unnamed: C5.1, R7.2
unnamed: R3.1, RV1.2, RV1.3
unnamed: R5.1, RV1.1, U1.2 (InA-)
unnamed: R5.2, R6.1, U1.1 (OutA)
unnamed: R6.2, U1.5 (InB+)
unnamed: R7.1, RV2.2, RV2.3
unnamed: R8.1, R9.1, U1.7 (OutB)
unnamed: R8.2, RV2.1, U1.6 (InB-)
unnamed: R9.2, T1.1 (AA), T1.3 (SA)
unnamed: T1.4 (SB), U2.1 (IN), U2.2 (IN)
RX5V: C6.1, C7.1, C8.1, R1.1, U1.8 (V+); also elsewhere on the board

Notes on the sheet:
Can also be 8V for more gain
